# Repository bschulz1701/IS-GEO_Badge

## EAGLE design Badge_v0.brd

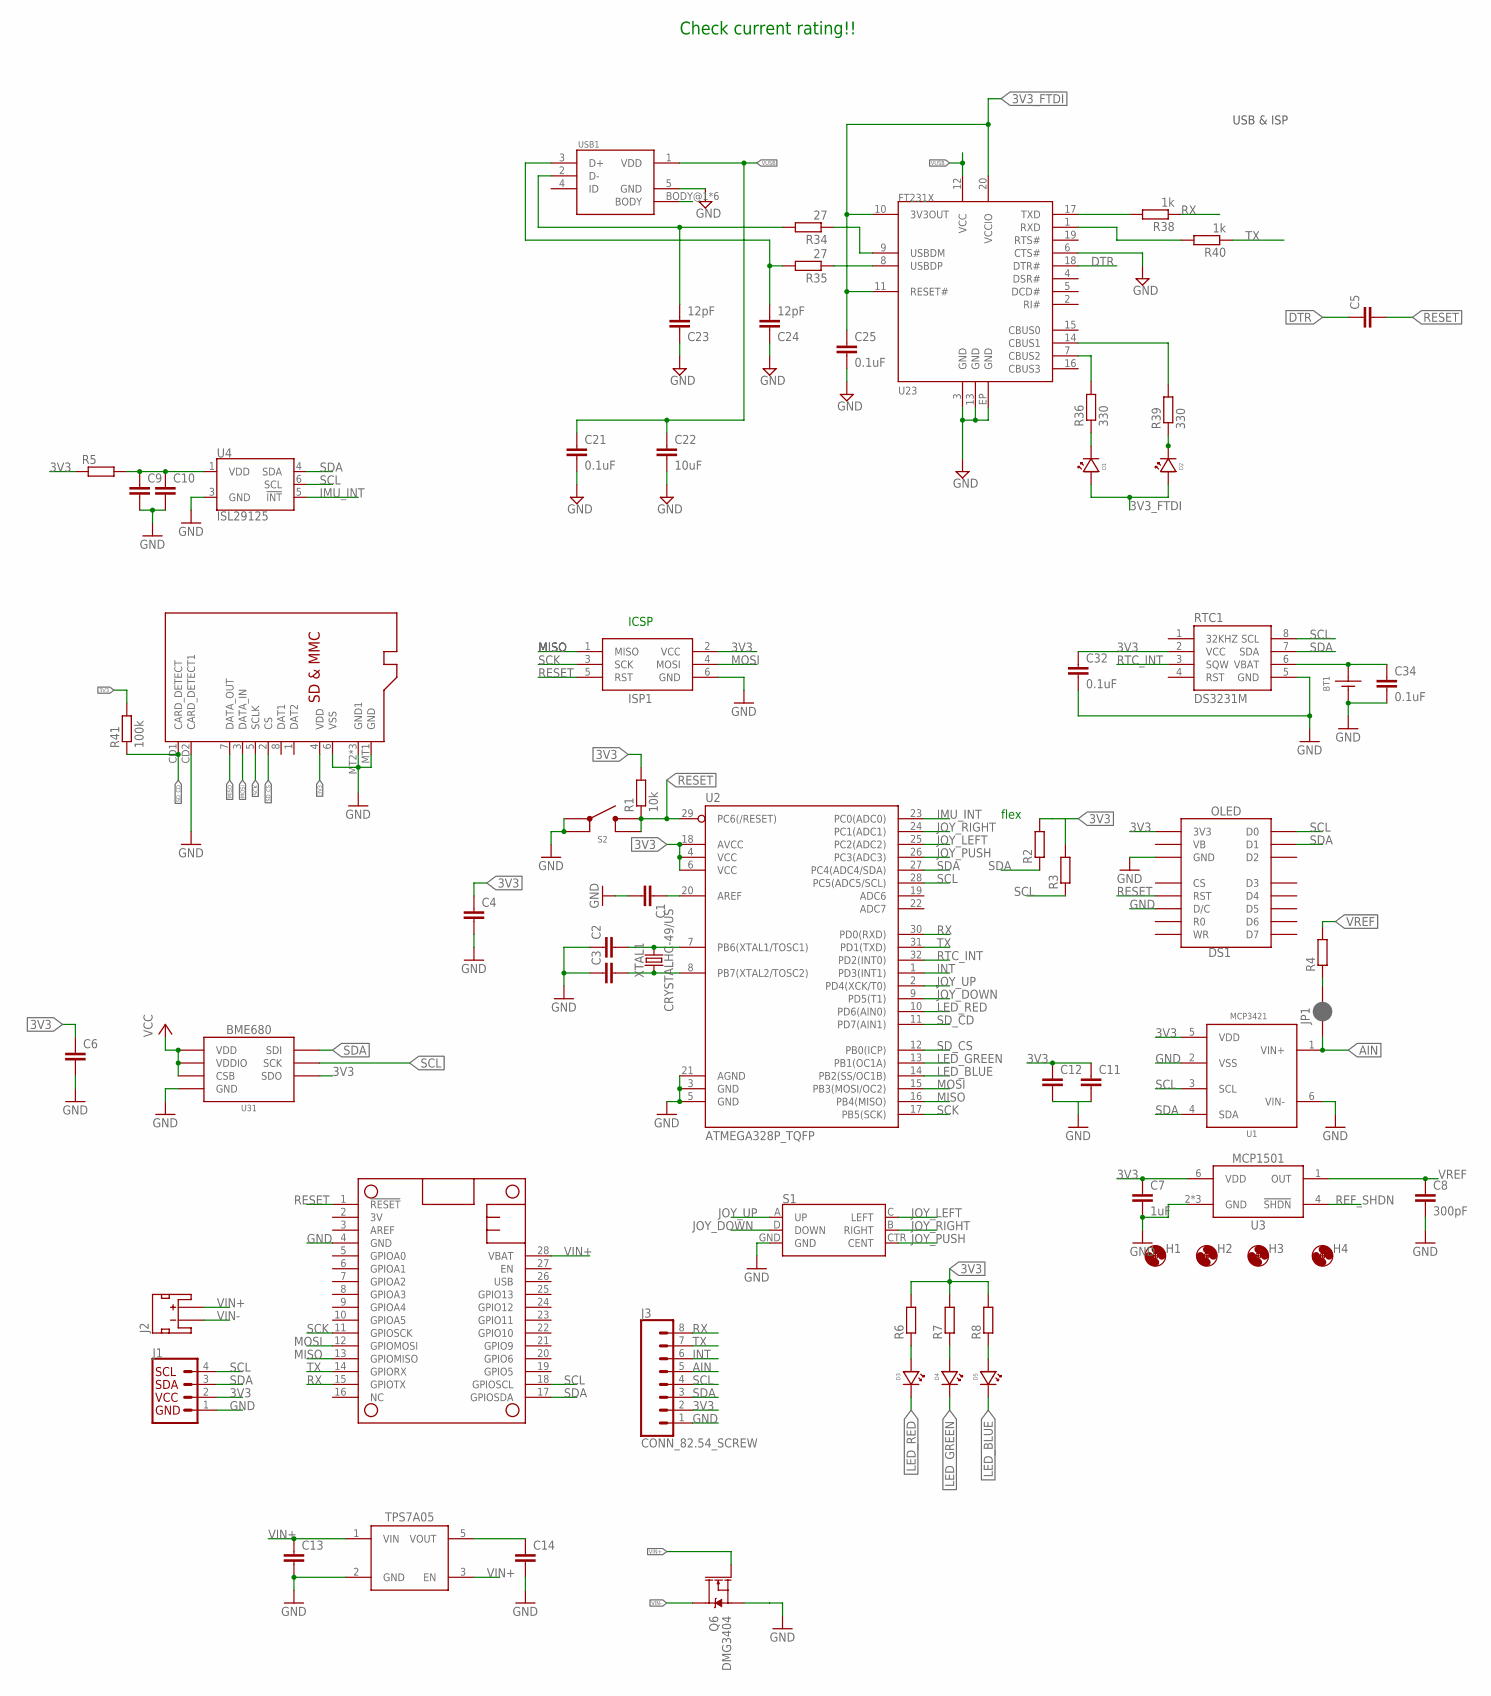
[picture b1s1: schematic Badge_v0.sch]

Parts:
BT1: BATTERY_COIN12MM; LINX_BAT-HLD-012-SMT
C1, C6, C10, C11: C-EU0.1UFC0603; C0603
C2, C3: C-EUC0603; C0603
C4, C9, C13, C14: C-EU1UFC0603; C0603
C5: C-EU0.1UFC0402; C0402
C7: 1uF; C0603
C8: 300pF; C0603
C12: C-EU10UFC0805; C0805
C21, C25, C32, C34: 0.1uF; C0402
C22: 10uF; C0805
C23, C24: 12pF; C0402
D1, D2, D3, D4, D5: LED0402; LED_0402
DS1: SAPRKFUN_MICRO_OLED; SPARKFUN_MICRO_OLED
H1, H2, H3, H4: MOUNTING_HOLE4_PL; 4_40_PLATED
ISP1: AVRISP-6; AVRISP; MPN 67997-206HLF; DIGIKEY 609-3234-ND
J1: QWIIC_CONNECTORJS-1MM; 1X04_1MM_RA
J2: JST_2MM_MALE; JST-2-SMD
J3: CONN_82.54_SCREW; 1X08_SCREW
JP1: JUMPER-SMT_2_NC_PASTE_SILK; SMT-JUMPER_2_NC_PASTE_SILK
MS1: FEATHERWINGLAYOUT; FEATHERWING_MIN
Q6: DMG3404; SOT23-3
R1: 10k; R0603
R2, R3: R-EU_10KR0603; R0603
R4: R-EU_P10KR0603; R0603
R5: R-EU_R0603; R0603
R6, R7, R8: R-EU_330R0402; R0402
R34, R35: 27; R0402
R36: 330; R0402; MPN RC0603FR-07330RL
R38, R40: 1k; R0402; MPN RC0603FR-07330RL
R39: 330; R0402; MPN RC0603FR-07330RL; DIGIKEY 311-330HRCT-ND
R41: 100k; R0402
RTC1: DS3231M; SO08
S1: JOYSTICK_MINI
S2: BUTTON; SWITCH_6MM
SD2: MICROSDCD; MICROSD_CD
U1: MCP3421A3; SOT23-6L
U2: ATMEGA328P_TQFP; TQFP32-08
U3: MCP15012.5V; SOT23-6L
U4: ISL29125; ODFN-6
U5: TPS7A0533DBV; SOT23-5
U23: FT231X-Q; QFN20
U31: BME680; BMP680
USB1: MICRO_USB_LONGPADS; 10118194-0001LF_10118194-0001LF_LONGER_PADS
XTAL1: CRYSTALHC-49/US; HC49UP

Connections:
3V3: C4.1, C6.1, C7.1, C11.1, C12.1, C14.1, C32.1, DS1.VDD (3V3), ISP1.2 (VCC), J1.2 (VCC), J3.2, R1.2, R2.2, R3.2, R5.1, R6.2, R7.2, R8.2, R41.2, RTC1.2 (VCC), SD2.4 (VDD), U1.5 (VDD), U2.4 (VCC), U2.6 (VCC), U2.18 (AVCC), U3.6 (VDD), U5.5 (VOUT), U31.2 (CSB), U31.5 (SDO), U31.6 (VDDIO), U31.8 (VDD)
3V3_FTDI: C25.1, D1.ANODE, D2.ANODE, U23.10 (3V3OUT), U23.11 (RESET#), U23.20 (VCCIO)
AIN: J3.5, JP1.1, U1.1 (VIN+)
DTR: C5.1, U23.18 (DTR#)
GND: BT1.GND (-), C1.2, C2.1, C3.1, C4.2, C6.2, C7.2, C8.2, C9.2, C10.2, C11.2, C12.2, C13.2, C14.2, C21.2, C22.2, C23.1, C24.1, C25.2, C32.2, C34.2, DS1.D/C, DS1.GND, ISP1.6 (GND), J1.1 (GND), J3.1, MS1.4 (GND), Q6.2 (S), RTC1.5 (GND), S1.GND, S2.1, S2.2, SD2.6 (VSS), SD2.CD2 (CARD_DETECT1), SD2.MT1 (GND), SD2.MT2 (GND1), SD2.MT3 (GND1), SD2.MT4 (GND1), U1.2 (VSS), U1.6 (VIN-), U2.3 (GND), U2.5 (GND), U2.21 (AGND), U3.2 (GND), U3.3 (GND), U3.5 (GND), U4.3 (GND), U5.2 (GND), U23.3 (GND), U23.6 (CTS#), U23.13 (GND), U23.EP (GND), U31.1 (GND), U31.7 (GND), USB1.5 (GND)
IMU_INT: U2.23 (PC0(ADC0)), U4.5 (!INT)
INT: J3.6, U2.1 (PD3(INT1))
JOY_DOWN: S1.D (DOWN), U2.9 (PD5(T1))
JOY_LEFT: S1.C (LEFT), U2.25 (PC2(ADC2))
JOY_PUSH: S1.CTR (CENT), U2.26 (PC3(ADC3))
JOY_RIGHT: S1.B (RIGHT), U2.24 (PC1(ADC1))
JOY_UP: S1.A (UP), U2.2 (PD4(XCK/T0))
LED_BLUE: D5.CATHODE, U2.14 (PB2(SS/OC1B))
LED_GREEN: D4.CATHODE, U2.13 (PB1(OC1A))
LED_RED: D3.CATHODE, U2.10 (PD6(AIN0))
MISO: ISP1.1 (MISO), MS1.13 (GPIOMISO), SD2.7 (DATA_OUT), U2.16 (PB4(MISO))
MOSI: ISP1.4 (MOSI), MS1.12 (GPIOMOSI), SD2.3 (DATA_IN), U2.15 (PB3(MOSI/OC2))
unnamed: USB1.BODY@1 (BODY), USB1.BODY@2 (BODY), USB1.BODY@3 (BODY), USB1.BODY@4 (BODY), USB1.BODY@7 (BODY), USB1.BODY@8 (BODY)
unnamed: JP1.2, R4.1
unnamed: C9.1, C10.1, R5.2, U4.1 (VDD)
unnamed: C1.1, U2.20 (AREF)
unnamed: C3.2, U2.8 (PB7(XTAL2/TOSC2)), XTAL1.1
unnamed: C2.2, U2.7 (PB6(XTAL1/TOSC1)), XTAL1.2
unnamed: D3.ANODE, R6.1
unnamed: D4.ANODE, R7.1
unnamed: D5.ANODE, R8.1
unnamed: BT1.POWER0 (+), BT1.POWER1 (+), C34.1, RTC1.6 (VBAT)
unnamed: R38.2, U23.17 (TXD)
unnamed: R40.2, U23.1 (RXD)
unnamed: C24.2, R35.2, USB1.3 (D+)
unnamed: C23.2, R34.2, USB1.2 (D-)
unnamed: R35.1, U23.8 (USBDP)
unnamed: R39.2, U23.14 (CBUS1)
unnamed: R34.1, U23.9 (USBDM)
unnamed: D2.CATHODE, R39.1
unnamed: D1.CATHODE, R36.1
unnamed: R36.2, U23.7 (CBUS2)
REF_SHDN: U3.4 (!SHDN)
RESET: C5.2, DS1.RESET (RST), ISP1.5 (RST), MS1.1 (!RESET), R1.1, S2.3, S2.4, U2.29 (PC6(/RESET))
RTC_INT: RTC1.3 (SQW), U2.32 (PD2(INT0))
RX: J3.8, MS1.15 (GPIOTX), R38.1, U2.30 (PD0(RXD))
SCK: ISP1.3 (SCK), MS1.11 (GPIOSCK), SD2.5 (SCLK), U2.17 (PB5(SCK))
SCL: DS1.D0/SCK (D0), J1.4 (SCL), J3.4, MS1.18 (GPIOSCL), R3.1, RTC1.8 (SCL), U1.3 (SCL), U2.28 (PC5(ADC5/SCL)), U4.6 (SCL), U31.4 (SCK)
SDA: DS1.D1/MOSI (D1), J1.3 (SDA), J3.3, MS1.17 (GPIOSDA), R2.1, RTC1.7 (SDA), U1.4 (SDA), U2.27 (PC4(ADC4/SDA)), U4.4 (SDA), U31.3 (SDI)
SD_CD: R41.1, SD2.CD1 (CARD_DETECT), U2.11 (PD7(AIN1))
SD_CS: SD2.2 (CS), U2.12 (PB0(ICP))
TX: J3.7, MS1.14 (GPIORX), R40.1, U2.31 (PD1(TXD))
VB: DS1.VBAT (VB)
VIN+: C13.1, J2.2 (+), MS1.28 (VBAT), Q6.1 (G), U5.1 (VIN), U5.3 (EN)
VIN-: J2.1 (-), Q6.3 (D)
VREF: C8.1, R4.2, U3.1 (OUT)
VUSB: C21.1, C22.1, U23.12 (VCC), USB1.1 (VDD)

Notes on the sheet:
ICSP
USB & ISP
Check current rating!!
flex

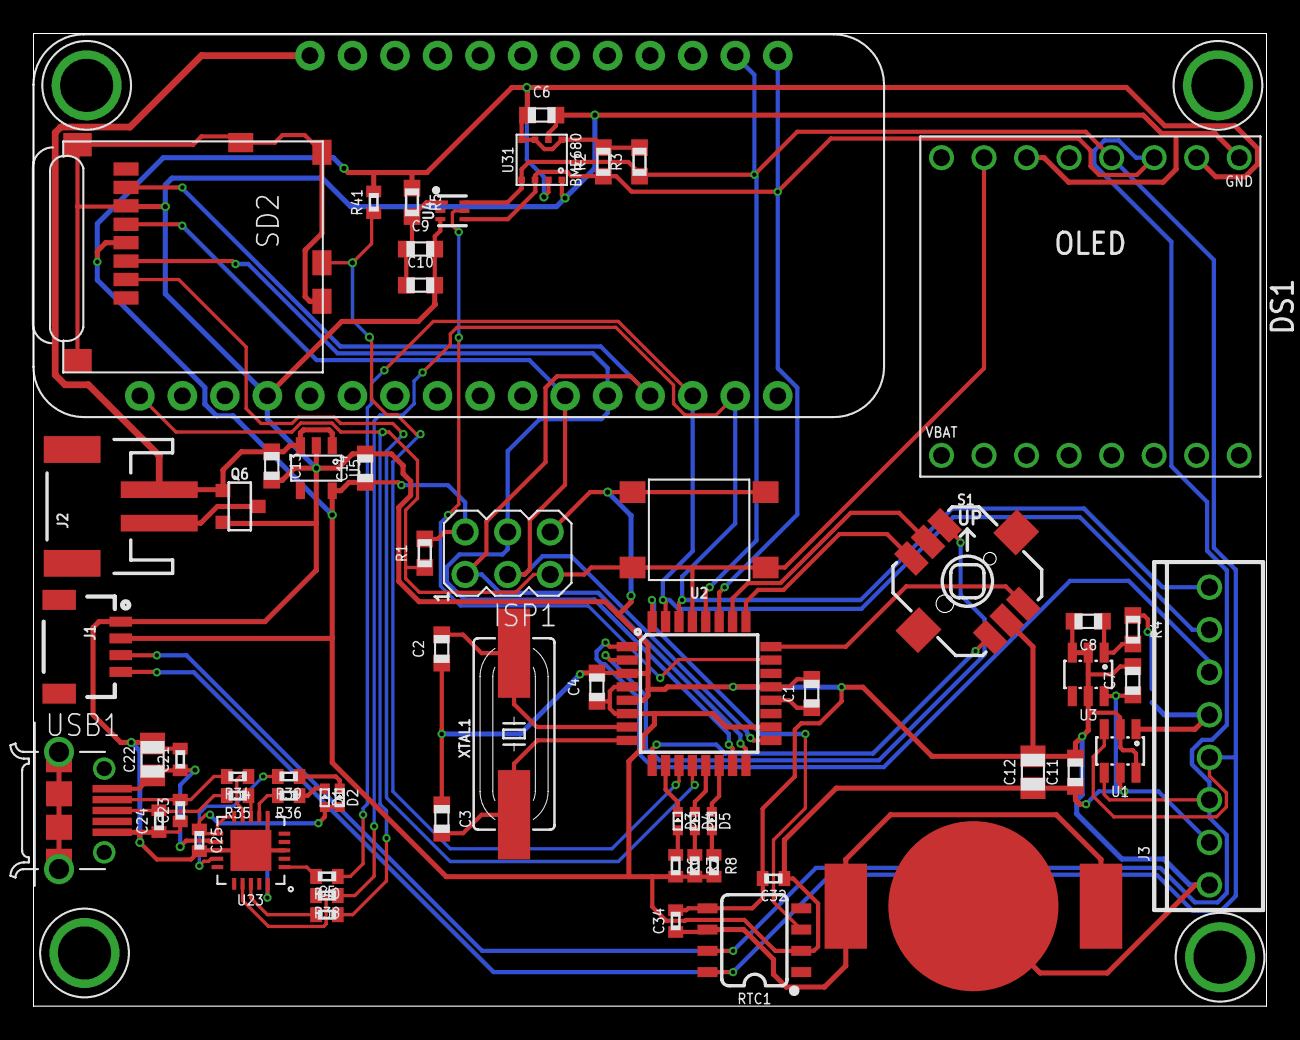
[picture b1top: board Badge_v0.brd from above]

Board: 2 copper layers, 73.6 x 58.1 mm, 67 parts (1 on the bottom side), 50 nets.

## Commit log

2019-06-06 Added licence
2019-06-06 Added readme, need to populate
2019-06-06 Incomplete schematic for v0 badge
2019-06-08 Initial routing, in progress
2019-06-13 Continued routing, functional
    Layout is functional but cleanup, details (silkscreen, part numbers, etc) and review still required

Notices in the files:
parts and their libraries:
SparkFun-Connectors: Licensing: Creative Commons ShareAlike 4.0 International - https://creativecommons.org/licenses/by-sa/4.0
